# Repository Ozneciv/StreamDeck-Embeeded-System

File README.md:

# ⌨️ StreamDeck Embedded System

> Periférico de entrada dedicado (*Macro Pad / Stream Deck*) de 9 teclas mecânicas baseado no microcontrolador ARM Cortex-M3 (STM32F103C8T6), desenvolvido com arquitetura orientada a interrupção de timer (100 Hz), comunicação USB Custom HID nativa e PCB em camada única.

---

## 📌 Visão Geral

Este repositório contém o código-fonte do firmware em C (STM32CubeIDE), projeto de hardware no KiCad (PCB Single-Layer `B.Cu` e arquivos Gerber), modelos 3D em STL da carcaça e o relatório técnico para a disciplina de **Sistemas Embarcados I** da **Universidade Federal de Uberlândia (UFU / FEELT)**.

---

## 🌟 Principais Características

- **⚡ Zero Polling:** Varredura da matriz 3x3 realizada por **Interrupção por Timer de Hardware (TIM2 a 100 Hz / 10 ms)** com repouso em baixo consumo (`__WFI()`).
- **🔄 Re-enumeração USB Automática:** Reset de software no pino USB D+ (`PA12`) na inicialização para identificação instantânea no SO após gravações.
- **🛡️ Anti-Ghosting:** Matriz 3x3 associada a 9 diodos $1\text{N}4148$.
- **🔌 Classe USB Custom HID:** Envio nativo de relatórios IN de 8 Bytes com atalhos de teclado (F13 a F21) e suporte a relatórios OUT bidirecionais.
- **📐 PCB Face Simples:** Placa projetada no KiCad em camada única (`B.Cu`) com trilhas reforçadas ($0.8\,\text{mm}$ a $1.2\,\text{mm}$) para fabricação por corrosão artesanal.
- **📦 Carcaça 3D:** Gabinete personalizado impresso em 3D com insertos roscados M3.

---

## 📷 Fotos do Projeto

<div align="center">

| Protótipo Finalizado | Montagem Física Interna |
| :---: | :---: |
|  |  |

</div>

---

## 🔌 Mapeamento de Pinos (Pinout STM32F103C8T6)

| Pino | Função | Modo GPIO / Periférico |
| :---: | :---: | :---: |
| **PA1, PA2, PA3** | Linhas 1 a 3 da Matriz | `GPIO_MODE_OUTPUT_OD` (Open Drain) |
| **PA4, PA5, PA6** | Colunas 1 a 3 da Matriz | `GPIO_MODE_INPUT` (Pull-Up Interno) |
| **PA11 / PA12** | USB D- / USB D+ | Periférico USB Custom HID |
| **PA13 / PA14** | SWDIO / SWCLK | Interface de Gravação e Depuração ST-LINK |

---

## 📂 Estrutura do Repositório

```text
├── streamdeck bluepill/        # Projeto STM32CubeIDE (Firmware C e arquivo .ioc)
├── PCB_FINAL/                  # Arquivos de fabricação KiCad e Gerbers finais
├── 3D/                         # Arquivos e modelos 3D STL do gabinete e teclas
├── dashboard/                  # Painel web interativo para testes e telemetria
├── StreamDeck_SEMB.pdf         # Relatório Técnico & Memorial Descritivo (PDF)
├── relatorio_streamdeck.tex    # Código-fonte em LaTeX do relatório
└── README.md                   # Documentação do projeto
```

---

## 🛠️ Como Compilar e Gravar o Firmware

1. **Requisitos:**
   - [STM32CubeIDE](https://www.st.com/en/development-tools/stm32cubeide.html) (v1.10 ou superior)
   - Gravador ST-LINK V2 ou via USB DFU Bootloader
2. **Passos:**
   - Abra o STM32CubeIDE e importe a pasta `streamdeck bluepill`.
   - Compile o projeto (`Project -> Build Project` ou `Ctrl+B`).
   - Conecte o ST-LINK à placa Blue Pill (SWDIO: PA13, SWCLK: PA14, GND, 3.3V).
   - Clique em `Run -> Debug` ou `Flash` para gravar o arquivo `.elf`.

---

## 👥 Equipe (Discentes / FEELT UFU)

- **Bruna de Jesus Silva** — `12021ETE007`
- **Gustavo Martins Ribeiro Moura** — `12111ETE002`
- **Mateus Henrique Gonçalves** — `12311ECP021`
- **Vicenzo De Marco Olivalves** — `12421ECP006`

**Docente Responsável:** Prof. Jeovane Vicente de Sousa  
**Curso:** Engenharia de Computação & Engenharia Eletrônica — UFU / FEELT  
**Ano:** 2026

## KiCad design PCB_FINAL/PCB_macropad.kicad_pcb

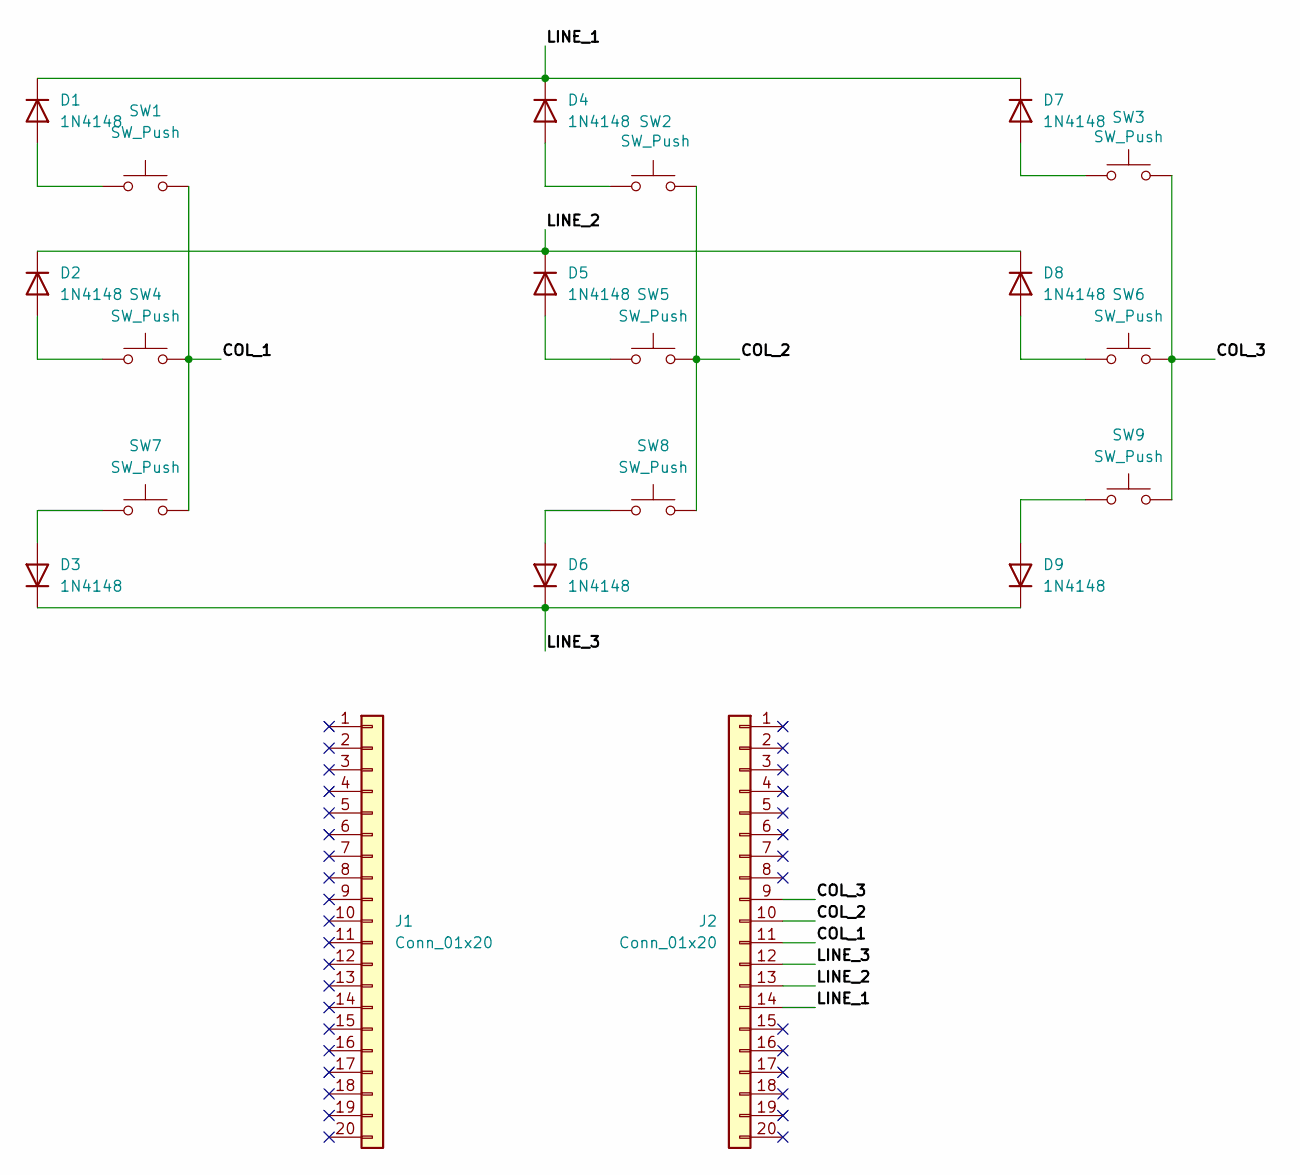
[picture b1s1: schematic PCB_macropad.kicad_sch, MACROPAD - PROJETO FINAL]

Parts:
D1, D2, D3, D4, D5, D6, D7, D8, D9: 1N4148; D_DO-35_SOD27_P7.62mm_Horizontal
J1, J2: Conn_01x20; PinHeader_1x20_P2.54mm_Vertical
SW1, SW2, SW3, SW4, SW5, SW6, SW7, SW8, SW9: SW_Push; SW_Cherry_MX_1.00u_PCB

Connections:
/COL_1: J2.11, SW1.2, SW4.2, SW7.2
/COL_2: J2.10, SW2.2, SW5.2, SW8.2
/COL_3: J2.9, SW3.2, SW6.2, SW9.2
/LINE_1: D1.1 (K), D4.1 (K), D7.1 (K), J2.14
/LINE_2: D2.1 (K), D5.1 (K), D8.1 (K), J2.13
/LINE_3: D3.1 (K), D6.1 (K), D9.1 (K), J2.12
unnamed: D1.2 (A), SW1.1
unnamed: D2.2 (A), SW4.1
unnamed: D3.2 (A), SW7.1
unnamed: D4.2 (A), SW2.1
unnamed: D5.2 (A), SW5.1
unnamed: D6.2 (A), SW8.1
unnamed: D7.2 (A), SW3.1
unnamed: D8.2 (A), SW6.1
unnamed: D9.2 (A), SW9.1

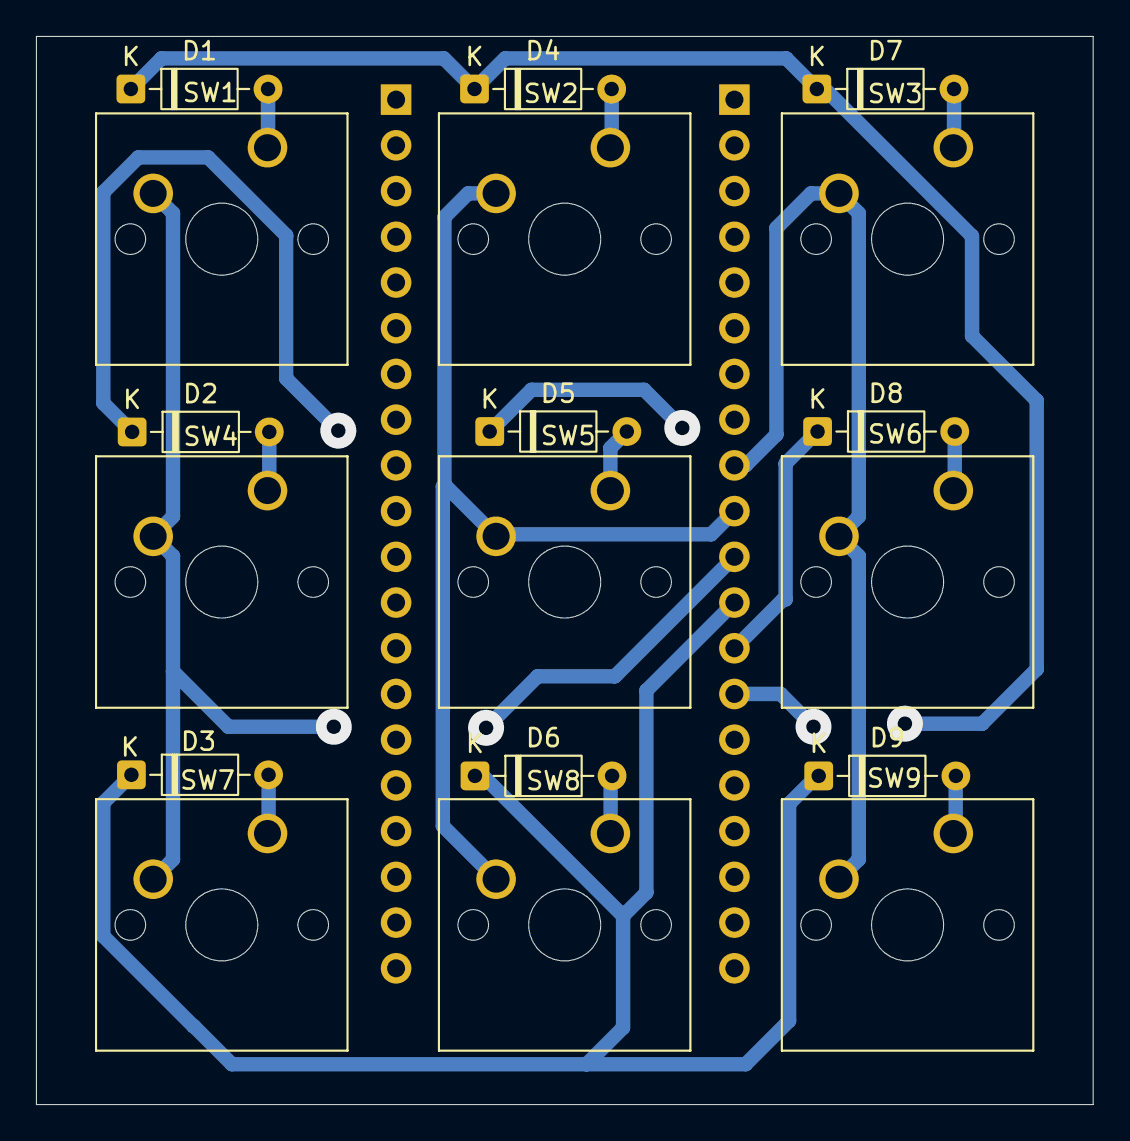
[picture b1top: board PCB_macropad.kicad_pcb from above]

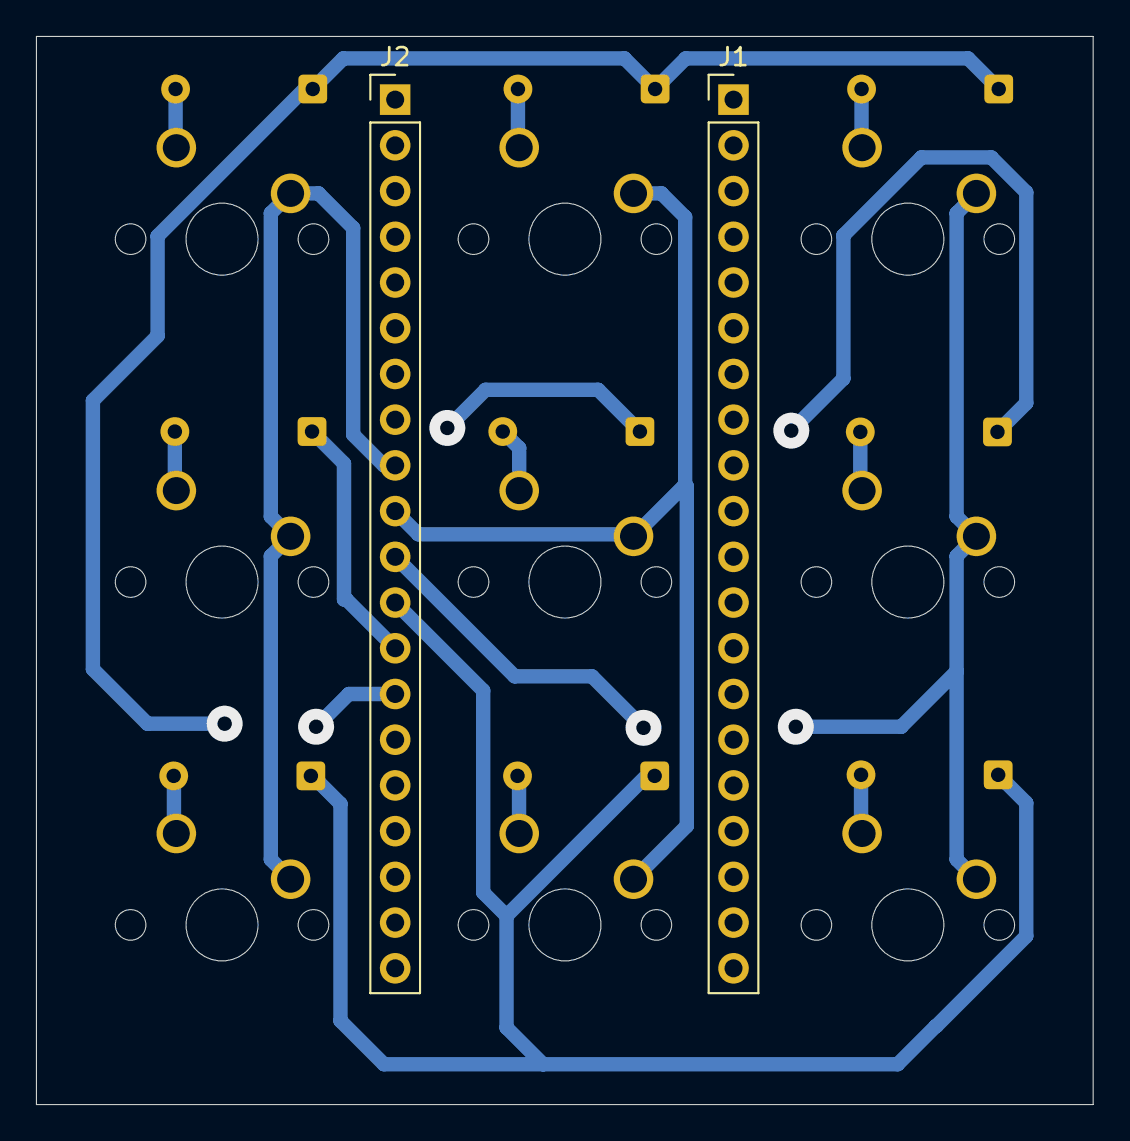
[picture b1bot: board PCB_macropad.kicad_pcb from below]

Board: 2 copper layers, 58.7 x 59.3 mm, 20 parts (2 on the bottom side), 15 nets.

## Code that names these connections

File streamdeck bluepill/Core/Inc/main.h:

/* USER CODE BEGIN Header */
/**
  ******************************************************************************
  * @file           : main.h
  * @brief          : Header for main.c file.
  *                   This file contains the common defines of the application.
  ******************************************************************************
  * @attention
  *
  * Copyright (c) 2026 STMicroelectronics.
  * All rights reserved.
  *
  * This software is licensed under terms that can be found in the LICENSE file
  * in the root directory of this software component.
  * If no LICENSE file comes with this software, it is provided AS-IS.
  *
  ******************************************************************************
  */
/* USER CODE END Header */

/* Define to prevent recursive inclusion -------------------------------------*/
#ifndef __MAIN_H
#define __MAIN_H

#ifdef __cplusplus
extern "C" {
#endif

/* Includes ------------------------------------------------------------------*/
#include "stm32f1xx_hal.h"

/* Private includes ----------------------------------------------------------*/
/* USER CODE BEGIN Includes */

/* USER CODE END Includes */

/* Exported types ------------------------------------------------------------*/
/* USER CODE BEGIN ET */

/* USER CODE END ET */

/* Exported constants --------------------------------------------------------*/
/* USER CODE BEGIN EC */

/* USER CODE END EC */

/* Exported macro ------------------------------------------------------------*/
/* USER CODE BEGIN EM */

/* USER CODE END EM */

/* Exported functions prototypes ---------------------------------------------*/
void Error_Handler(void);

/* USER CODE BEGIN EFP */

/* USER CODE END EFP */

/* Private defines -----------------------------------------------------------*/
#define LINE_1_Pin GPIO_PIN_1
#define LINE_1_GPIO_Port GPIOA
#define LINE_2_Pin GPIO_PIN_2
#define LINE_2_GPIO_Port GPIOA
#define LINE_3_Pin GPIO_PIN_3
#define LINE_3_GPIO_Port GPIOA
#define COL_1_Pin GPIO_PIN_4
#define COL_1_GPIO_Port GPIOA
#define COL_2_Pin GPIO_PIN_5
#define COL_2_GPIO_Port GPIOA
#define COL_3_Pin GPIO_PIN_6
#define COL_3_GPIO_Port GPIOA

/* USER CODE BEGIN Private defines */

/* USER CODE END Private defines */

#ifdef __cplusplus
}
#endif

#endif /* __MAIN_H */
